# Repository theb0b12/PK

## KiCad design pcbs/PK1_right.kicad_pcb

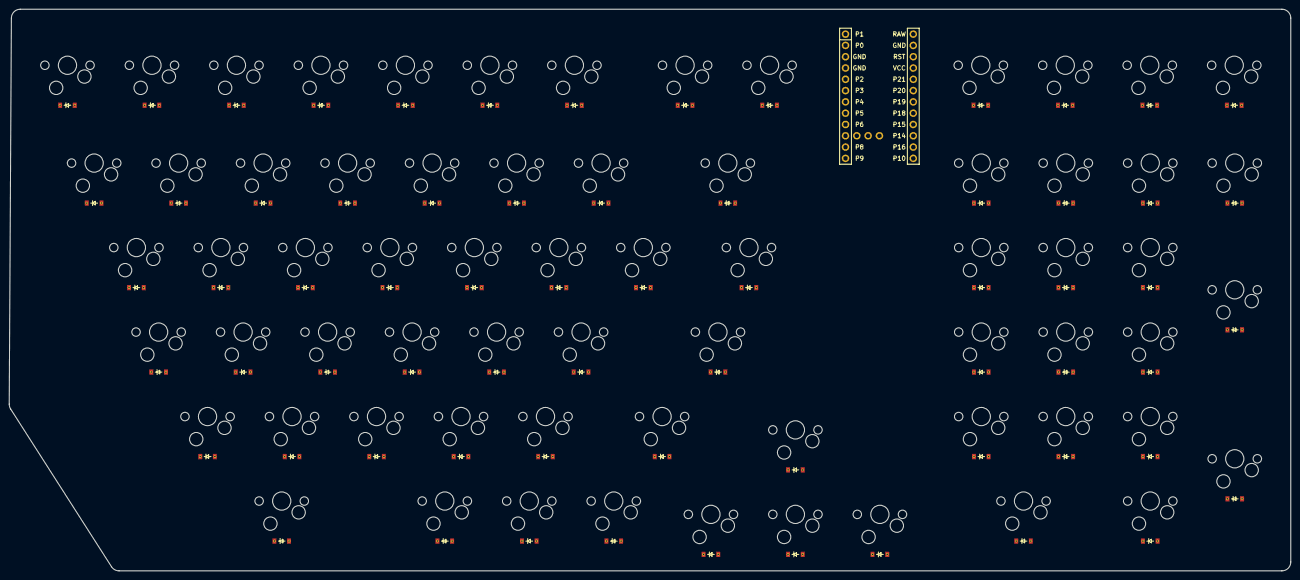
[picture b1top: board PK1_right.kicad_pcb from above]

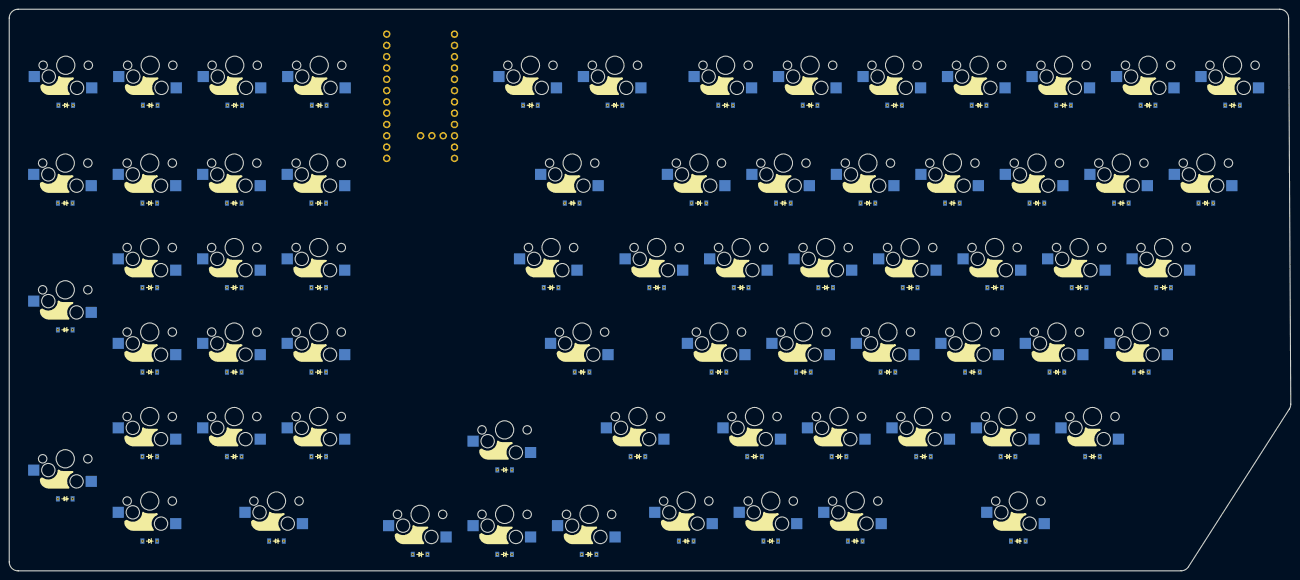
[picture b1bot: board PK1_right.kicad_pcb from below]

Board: 2 copper layers, 288.2 x 126.3 mm, 135 parts (67 on the bottom side), 85 nets, no tracks yet.

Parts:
D1, D2, D3, D4, D5, D6, D7, D8, D9, D10, D11, D12, D13, D14, D15, D16, D17, D18, D19, D20, D21, D22, D23, D24, D25, D26, D27, D28, D29, D30, D31, D32, D33, D34, D35, D36, D37, D38, D39, D40, D41, D42, D43, D44, D45, D46, D47, D48, D49, D50, D51, D52, D53, D54, D55, D56, D57, D58, D59, D60, D61, D62, D63, D64, D65, D66, D67: ComboDiode
MCU1: mcu_nice_nano
S1, S2, S3, S4, S5, S6, S7, S8, S9, S10, S11, S12, S13, S14, S15, S16, S17, S18, S19, S20, S21, S22, S23, S24, S25, S26, S27, S28, S29, S30, S31, S32, S33, S34, S35, S36, S37, S38, S39, S40, S41, S42, S43, S44, S45, S46, S47, S48, S49, S50, S51, S52, S53, S54, S55, S56, S57, S58, S59, S60, S61, S62, S63, S64, S65, S66, S67: switch_mx

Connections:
0_single: D66.1, D66.2, S66.2
1_single: D62.1, D62.2, S62.2
2_single: D63.1, D63.2, S63.2
3_single: D64.1, D64.2, S64.2
4_single: D59.1, D59.2, S59.2
5_single: D60.1, D60.2, S60.2
6_single: D61.1, D61.2, S61.2
7_single: D55.1, D55.2, S55.2
8_single: D56.1, D56.2, S56.2
9_single: D57.1, D57.2, S57.2
GND: MCU1.2, MCU1.21, MCU1.22
P0: MCU1.23, S1.1, S14.1, S22.1, S30.1, S37.1, S43.1
P1: MCU1.24, S2.1, S15.1, S23.1, S31.1, S38.1, S44.1
P2: MCU1.20, S3.1, S16.1, S24.1, S32.1, S39.1, S45.1
P3: MCU1.19, S4.1, S17.1, S25.1, S33.1, S40.1, S46.1
P4: MCU1.18, S5.1, S18.1, S26.1, S34.1, S41.1, S48.1
P5: MCU1.17, S6.1, S19.1, S27.1, S35.1, S42.1, S49.1
P6: MCU1.16, S7.1, S20.1, S28.1, S36.1, S47.1, S50.1
P7: MCU1.15, S8.1, S21.1, S29.1, S59.1, S62.1, S66.1
P8: MCU1.14, S9.1, S51.1, S55.1, S60.1, S63.1, S67.1
P9: MCU1.13, S10.1, S52.1, S56.1, S61.1, S64.1
P10: MCU1.12, S11.1, S53.1, S57.1, S65.1
P11: MCU1.25, S12.1, S54.1, S58.1
P12: MCU1.26, S13.1
P13: D1.1, D2.1, D3.1, D4.1, D5.1, D6.1, D7.1, D8.1, D9.1, D10.1, D11.1, D12.1, D13.1, MCU1.27
P14: D14.1, D15.1, D16.1, D17.1, D18.1, D19.1, D20.1, D21.1, D51.1, D52.1, D53.1, D54.1, MCU1.10
P15: D22.1, D23.1, D24.1, D25.1, D26.1, D27.1, D28.1, D29.1, D55.1, D56.1, D57.1, D58.1, MCU1.9
P16: D30.1, D31.1, D32.1, D33.1, D34.1, D35.1, D36.1, D59.1, D60.1, D61.1, MCU1.11
P17: D37.1, D38.1, D39.1, D40.1, D41.1, D42.1, D47.1, D62.1, D63.1, D64.1, D65.1
P18: D43.1, D44.1, D45.1, D46.1, D48.1, D49.1, D50.1, D66.1, D67.1, MCU1.8
backslash_single: D29.1, D29.2, S29.2
backspc_single: D21.1, D21.2, S21.2
bracket1_single: D27.1, D27.2, S27.2
bracket2_single: D28.1, D28.2, S28.2
colon_single: D34.1, D34.2, S34.2
comma_single: D39.1, D39.2, S39.2
delete_single: D9.1, D9.2, S9.2
dot_single: D67.1, D67.2, S67.2
down_single: D49.1, D49.2, S49.2
enter_single: D36.1, D36.2, D65.1, D65.2, S36.2, S65.2
equals_single: D20.1, D20.2, S20.2
fn_single: D45.1, D45.2, S45.2
func6_single: D1.1, D1.2, S1.2
func7_single: D2.1, D2.2, S2.2
func8_single: D3.1, D3.2, S3.2
func9_single: D4.1, D4.2, S4.2
func10_single: D5.1, D5.2, S5.2
func11_single: D6.1, D6.2, S6.2
func12_single: D7.1, D7.2, S7.2
h_single: D30.1, D30.2, S30.2
home_single: D10.1, D10.2, S10.2
hyphen_single: D19.1, D19.2, S19.2
i_single: D24.1, D24.2, S24.2
insert_single: D11.1, D11.2, S11.2
j_single: D31.1, D31.2, S31.2
k_single: D32.1, D32.2, S32.2
l_single: D33.1, D33.2, S33.2
left_single: D48.1, D48.2, S48.2
m_single: D38.1, D38.2, S38.2
minus_single: D54.1, D54.2, S54.2
n_single: D37.1, D37.2, S37.2
num6_single: D14.1, D14.2, S14.2
num7_single: D15.1, D15.2, S15.2
num8_single: D16.1, D16.2, S16.2
num9_single: D17.1, D17.2, S17.2
num10_single: D18.1, D18.2, S18.2
num_single: D51.1, D51.2, S51.2
o_single: D25.1, D25.2, S25.2
p_single: D26.1, D26.2, S26.2
period_single: D40.1, D40.2, S40.2
pgdn_single: D13.1, D13.2, S13.2
pgup_single: D12.1, D12.2, S12.2
plus_single: D58.1, D58.2, S58.2
printscreen_single: D8.1, D8.2, S8.2
quotes_single: D35.1, D35.2, S35.2
rcntrl_single: D46.1, D46.2, S46.2
right_single: D50.1, D50.2, S50.2
rightalt_single: D44.1, D44.2, S44.2
shift_single: D42.1, D42.2, S42.2
slash_single: D41.1, D41.2, D52.1, D52.2, S41.2, S52.2
space_single: D43.1, D43.2, S43.2
star_single: D53.1, D53.2, S53.2
u_single: D23.1, D23.2, S23.2
up_single: D47.1, D47.2, S47.2
y_single: D22.1, D22.2, S22.2

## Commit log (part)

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2026-06-25 added right and renamed
2026-06-25 updated the name because its right
2026-06-25 made the pcb work
2026-06-26 added more keys
2026-06-26 added outline one
2026-06-27 updated and cleaned it up
2026-06-27 removed unneeded pcb things
2026-06-27 Modify stack operation points in PK1_right.yaml
    Updated references and shifts for stack operation points in PK1_right.yaml.
